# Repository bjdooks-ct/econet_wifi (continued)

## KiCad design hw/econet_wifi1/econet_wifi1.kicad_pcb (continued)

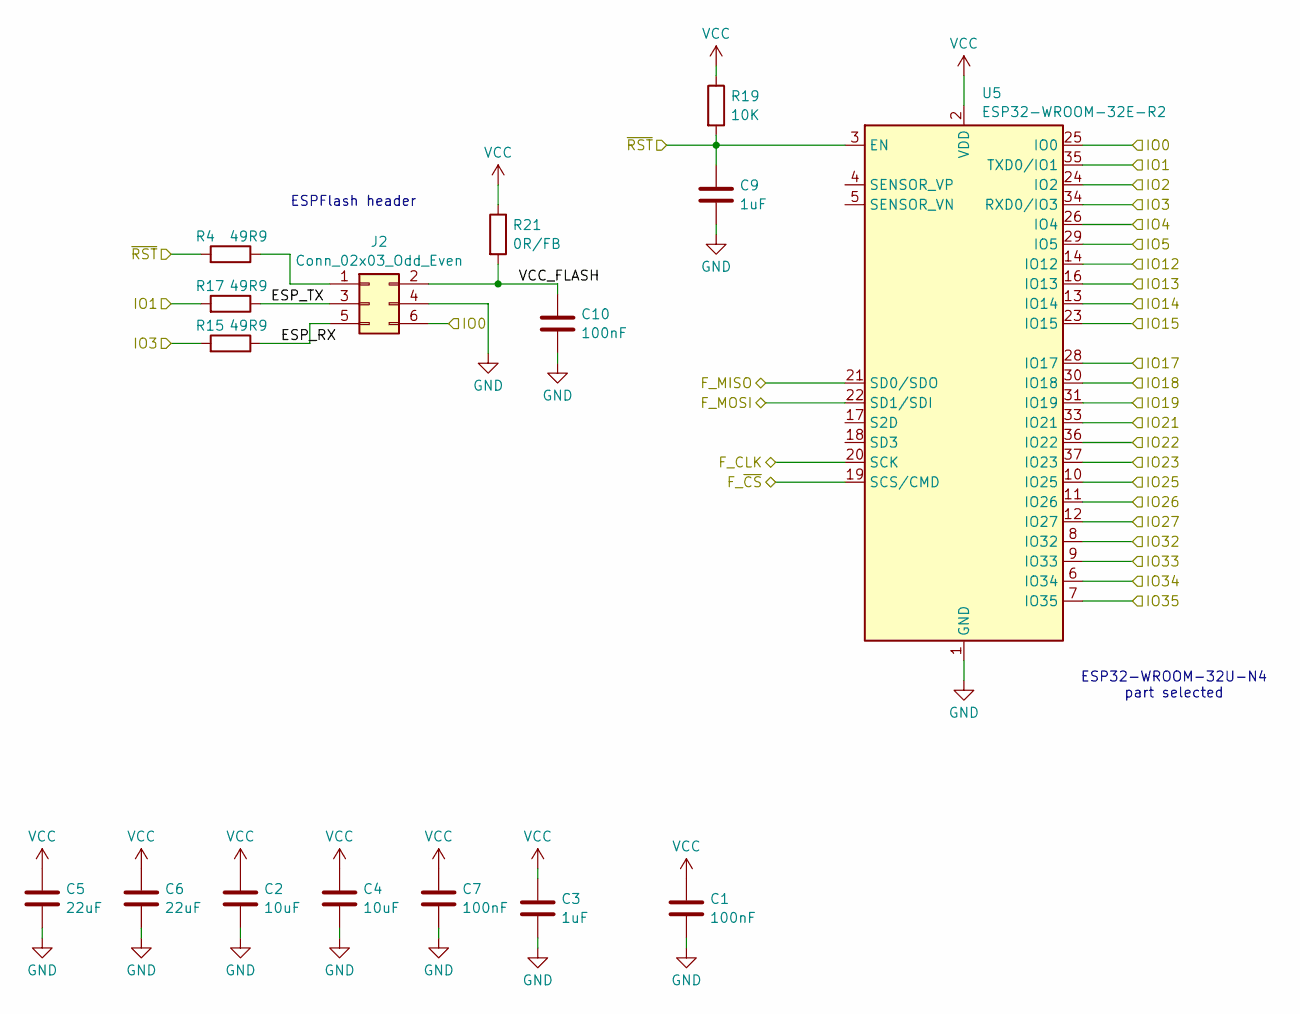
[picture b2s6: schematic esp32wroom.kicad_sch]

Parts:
C1, C7: 100nF; C_0402_1005Metric_Pad0.74x0.62mm_HandSolder; LCSC C1525
C2, C4: 10uF; C_0805_2012Metric_Pad1.18x1.45mm_HandSolder; LCSC C440198
C3, C9: 1uF; C_0402_1005Metric_Pad0.74x0.62mm_HandSolder; LCSC C52923
C5, C6: 22uF; C_0805_2012Metric_Pad1.18x1.45mm_HandSolder; LCSC C45783
C10: 100nF; C_0603_1608Metric_Pad1.08x0.95mm_HandSolder; LCSC C14663
J2: Conn_02x03_Odd_Even; PinHeader_2x03_P2.54mm_Vertical
R4, R15, R17: 49R9; R_0603_1608Metric_Pad0.98x0.95mm_HandSolder; LCSC C25120
R19: 10K; R_0603_1608Metric_Pad0.98x0.95mm_HandSolder; LCSC C25804
R21: 0R/FB; R_0603_1608Metric_Pad0.98x0.95mm_HandSolder; LCSC C21189
U5: ESP32-WROOM-32E-R2; ESP32-WROOM-32D; LCSC C328062

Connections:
/ESP_IO0: J2.6, U5.25 (IO0); also elsewhere on the board
/ESP_LED: U5.11 (IO26); also elsewhere on the board
/ESP_SRX: R15.2, U5.34 (RXD0/IO3)
/ESP_STX: R17.2, U5.35 (TXD0/IO1)
/HSPI_CLK: U5.13 (IO14); also elsewhere on the board
/HSPI_D: U5.16 (IO13); also elsewhere on the board
/HSPI_Q: U5.14 (IO12); also elsewhere on the board
/HSPI_~CS: U5.23 (IO15); also elsewhere on the board
/VSPI_CLK: U5.30 (IO18); also elsewhere on the board
/VSPI_D: U5.37 (IO23); also elsewhere on the board
/VSPI_Q: U5.31 (IO19)
/VSPI_~CS: U5.29 (IO5); also elsewhere on the board
/esp32wroom/ESP_RX: J2.5, R15.1
/esp32wroom/ESP_TX: J2.3, R17.1
/esp32wroom/F_CLK: U5.20 (SCK); also elsewhere on the board
/esp32wroom/F_MISO: U5.21 (SD0/SDO); also elsewhere on the board
/esp32wroom/F_MOSI: U5.22 (SD1/SDI); also elsewhere on the board
/esp32wroom/F_~CS: U5.19 (SCS/CMD); also elsewhere on the board
/esp32wroom/IO2: U5.24 (IO2)
/esp32wroom/IO4: U5.26 (IO4)
/esp32wroom/IO17: U5.28 (IO17)
/esp32wroom/IO21: U5.33 (IO21)
/esp32wroom/IO22: U5.36 (IO22)
/esp32wroom/IO25: U5.10 (IO25)
/esp32wroom/IO27: U5.12 (IO27); also elsewhere on the board
/esp32wroom/IO32: U5.8 (IO32); also elsewhere on the board
/esp32wroom/IO33: U5.9 (IO33); also elsewhere on the board
/esp32wroom/IO34: U5.6 (IO34); also elsewhere on the board
/esp32wroom/IO35: U5.7 (IO35); also elsewhere on the board
/esp32wroom/VCC_FLASH: C10.1, J2.2, R21.2
/~RST_ESP: C9.1, R4.2, R19.2, U5.3 (EN); also elsewhere on the board
GND: C1.2, C2.2, C3.2, C4.2, C5.2, C6.2, C7.2, C9.2, C10.2, J2.4, U5.1 (GND), U5.15 (GND), U5.38 (GND), U5.39 (GND); also elsewhere on the board
unnamed: J2.1, R4.1
VCC: C1.1, C2.1, C3.1, C4.1, C5.1, C6.1, C7.1, R19.1, R21.1, U5.2 (VDD); also elsewhere on the board

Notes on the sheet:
ESPFlash header
ESP32-WROOM-32U-N4 part selected

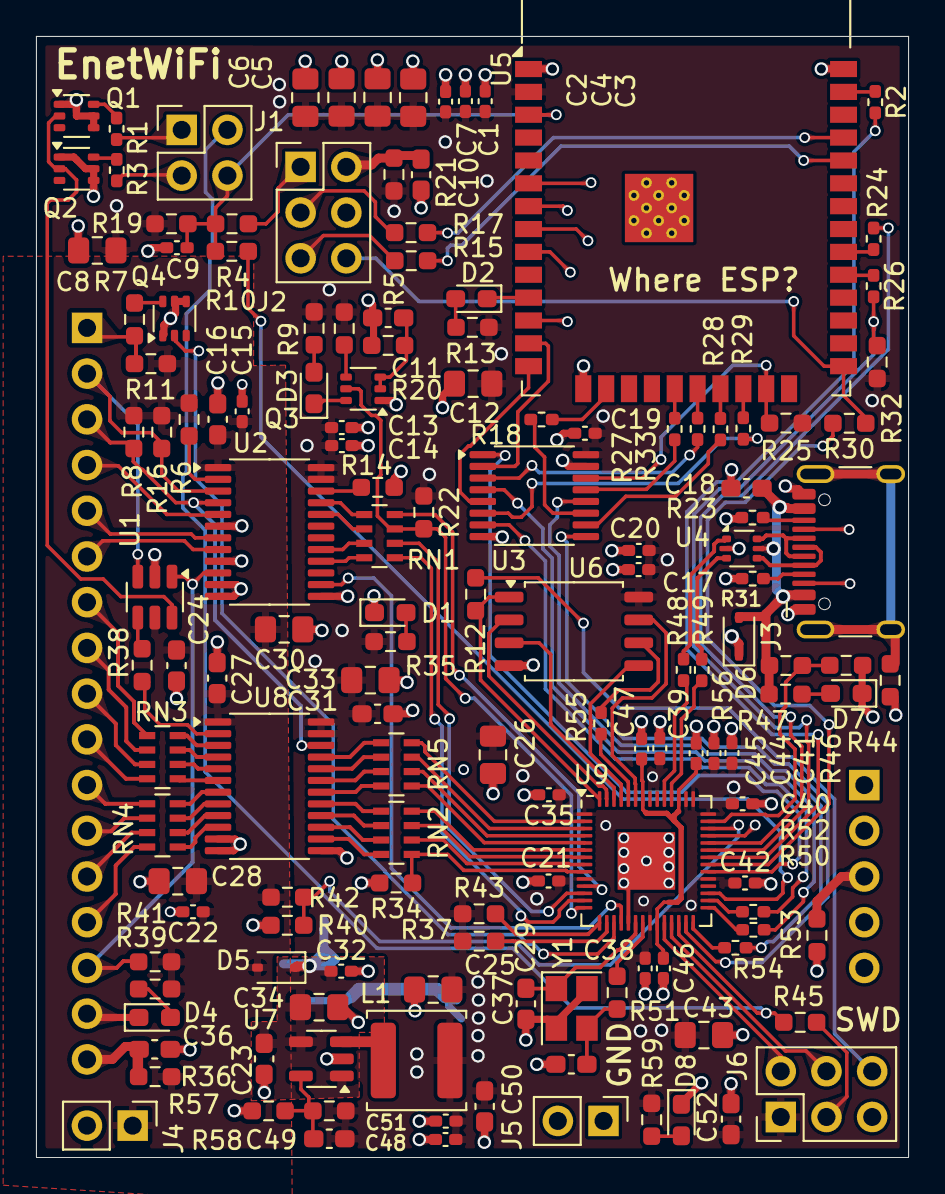
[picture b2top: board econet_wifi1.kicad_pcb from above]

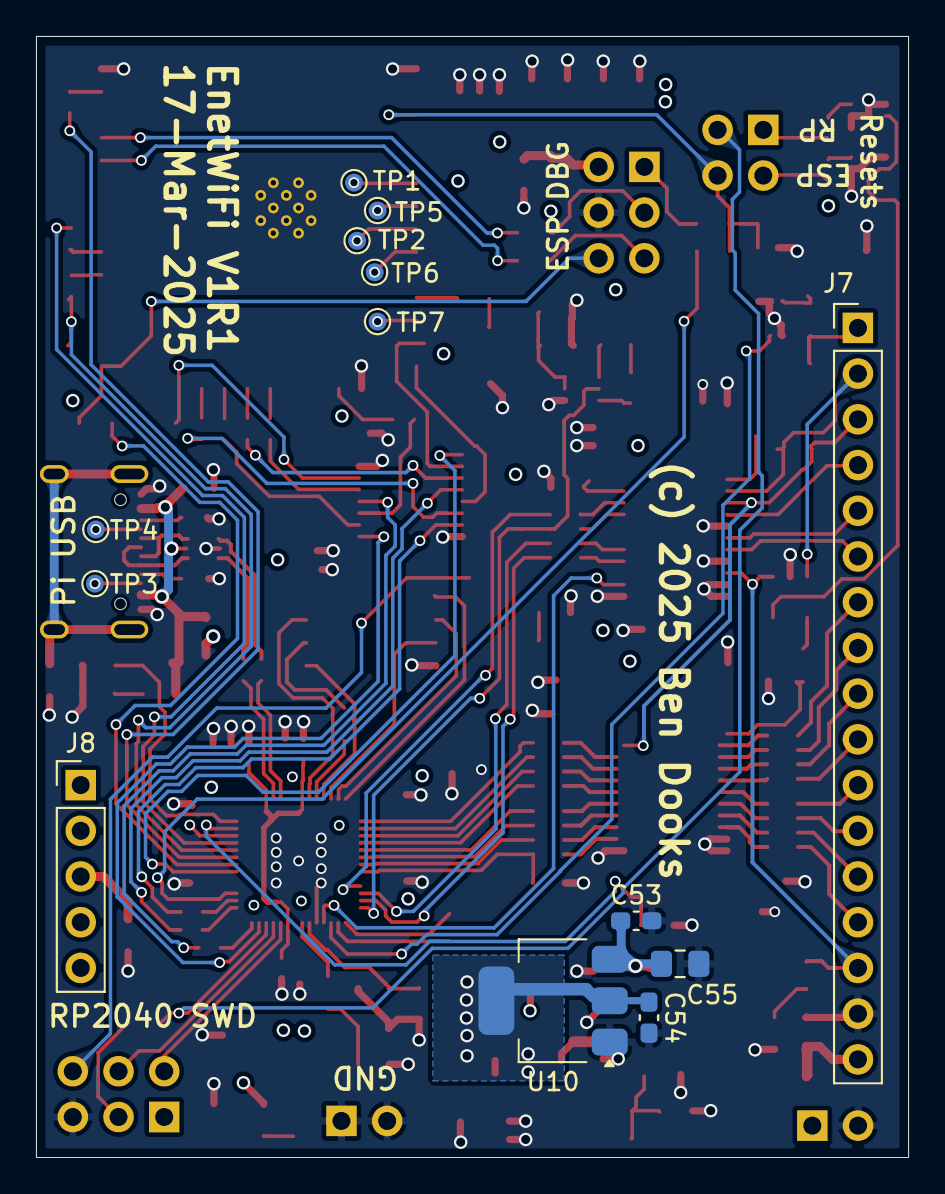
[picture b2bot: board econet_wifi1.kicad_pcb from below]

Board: 4 copper layers, 48.5 x 62.3 mm, 158 parts (13 on the bottom side), 152 nets.

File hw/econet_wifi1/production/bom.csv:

Designator,Footprint,Quantity,Value,LCSC Part #
"C1, C14, C17, C19, C21, C35, C38, C39, C40, C41, C42, C46, C47, C7",0402,14,100nF,C1525
"C10, C11, C16, C18, C23, C24, C27, C31, C36, C50, C52",0603,11,100nF,C14663
"C12, C2, C25, C26, C28, C30, C33, C34, C4, C43, C8",0805,11,10uF,C440198
"C13, C15, C20, C22, C3, C32, C44, C45, C48, C51, C9",0402,11,1uF,C52923
"C29, C37, C49",0603,3,15pF,C1644
"C5, C6",0805,2,22uF,C45783
"D1, D2, D3, D4, D7, D8",0603,6,LED_Small_Filled,C2286
"D5, D6",D_SOD-323,2,1N5819WS,C191023
J1,PinHeader_2x02_P2.54mm_Vertical,1,Conn_02x02_Odd_Even,
"J2, J6",PinHeader_2x03_P2.54mm_Vertical,2,Conn_02x03_Odd_Even,
J3,USB_C_Receptacle_HCTL_HC-TYPE-C-16P-01A,1,USB_C_Receptacle_USB2.0_16P,C2894897
"J4, J5",PinHeader_1x02_P2.54mm_Vertical,2,Conn_01x02_Pin,
J7,PinHeader_1x17_P2.54mm_Vertical,1,Conn_01x17_Pin,
J8,PinHeader_1x05_P2.54mm_Vertical,1,Conn_01x05_Pin,
L1,L_APV_ANR5040,1,3.3uH 3.6A (SWPA4030S3R3MT),C15269
"Q1, Q2, Q3, Q4",SOT-363_SC-70-6,4,DMC3400SDW,C155499
"R1, R18, R2, R24, R26, R27, R28, R29, R3, R33, R50, R52, R54",0402,13,33R,C17634
"R10, R12, R30, R37, R39, R43, R47, R51",0603,8,1K,C21190
"R11, R34, R56, R58",0603,4,4K7,C23162
"R13, R35, R38, R5, R59, R9",0603,6,560R,C23204
"R14, R19, R20, R22, R25, R32, R40, R42, R44, R6, R8",0603,11,10K,C25804
"R15, R17, R4, R45, R7",0603,5,49R9,C25120
"R16, R41",0603,2,100K,C25803
"R21, R36, R46, R53",0603,4,0R/FB,C21189
"R23, R31",0402,2,5K1,C25905
"R48, R49, R55",0402,3,27R,C25100
R57,0603,1,21K,C22956
"RN1, RN2, RN3, RN4, RN5",R_Array_Concave_4x0603,5,RP_47R,C1980
"TP1, TP2, TP3, TP4, TP5, TP6, TP7",TestPoint_Pad_D1.0mm,7,TestPoint,
U1,SOT-23-6,1,SN74LVC2G14DBV,C12401
"U2, U8",TSSOP-24_4.4x7.8mm_P0.65mm,2,SN74AVC8T245PW,C1523276
U3,TSSOP-16_4.4x5mm_P0.65mm,1,74CBTLV3257,C7637
U4,SOT-666,1,USBLC6-2P6,C5180249
U5,ESP32-WROOM-32D,1,ESP32-WROOM-32E-R2,C328062
U6,SOIC-8_5.23x5.23mm_P1.27mm,1,W25Q128JVS,
U7,SOT-23-5,1,LP3201AB5,C2890377
U9,QFN-56-1EP_7x7mm_P0.4mm_EP3.2x3.2mm,1,RP2040,
Y1,Crystal_SMD_Abracon_ABM8G-4Pin_3.2x2.5mm,1,Crystal_GND24,C20625731

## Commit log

2025-03-27 initial hw from first release
2025-03-27 initial project readme
2025-03-27 import of initial adapter for Acorn A4
